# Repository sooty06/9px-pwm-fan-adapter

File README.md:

# 9px-pwm-fan-adapter
PWM fan adapter for replacing the stock fans in an Eaton 9PX series UPS.

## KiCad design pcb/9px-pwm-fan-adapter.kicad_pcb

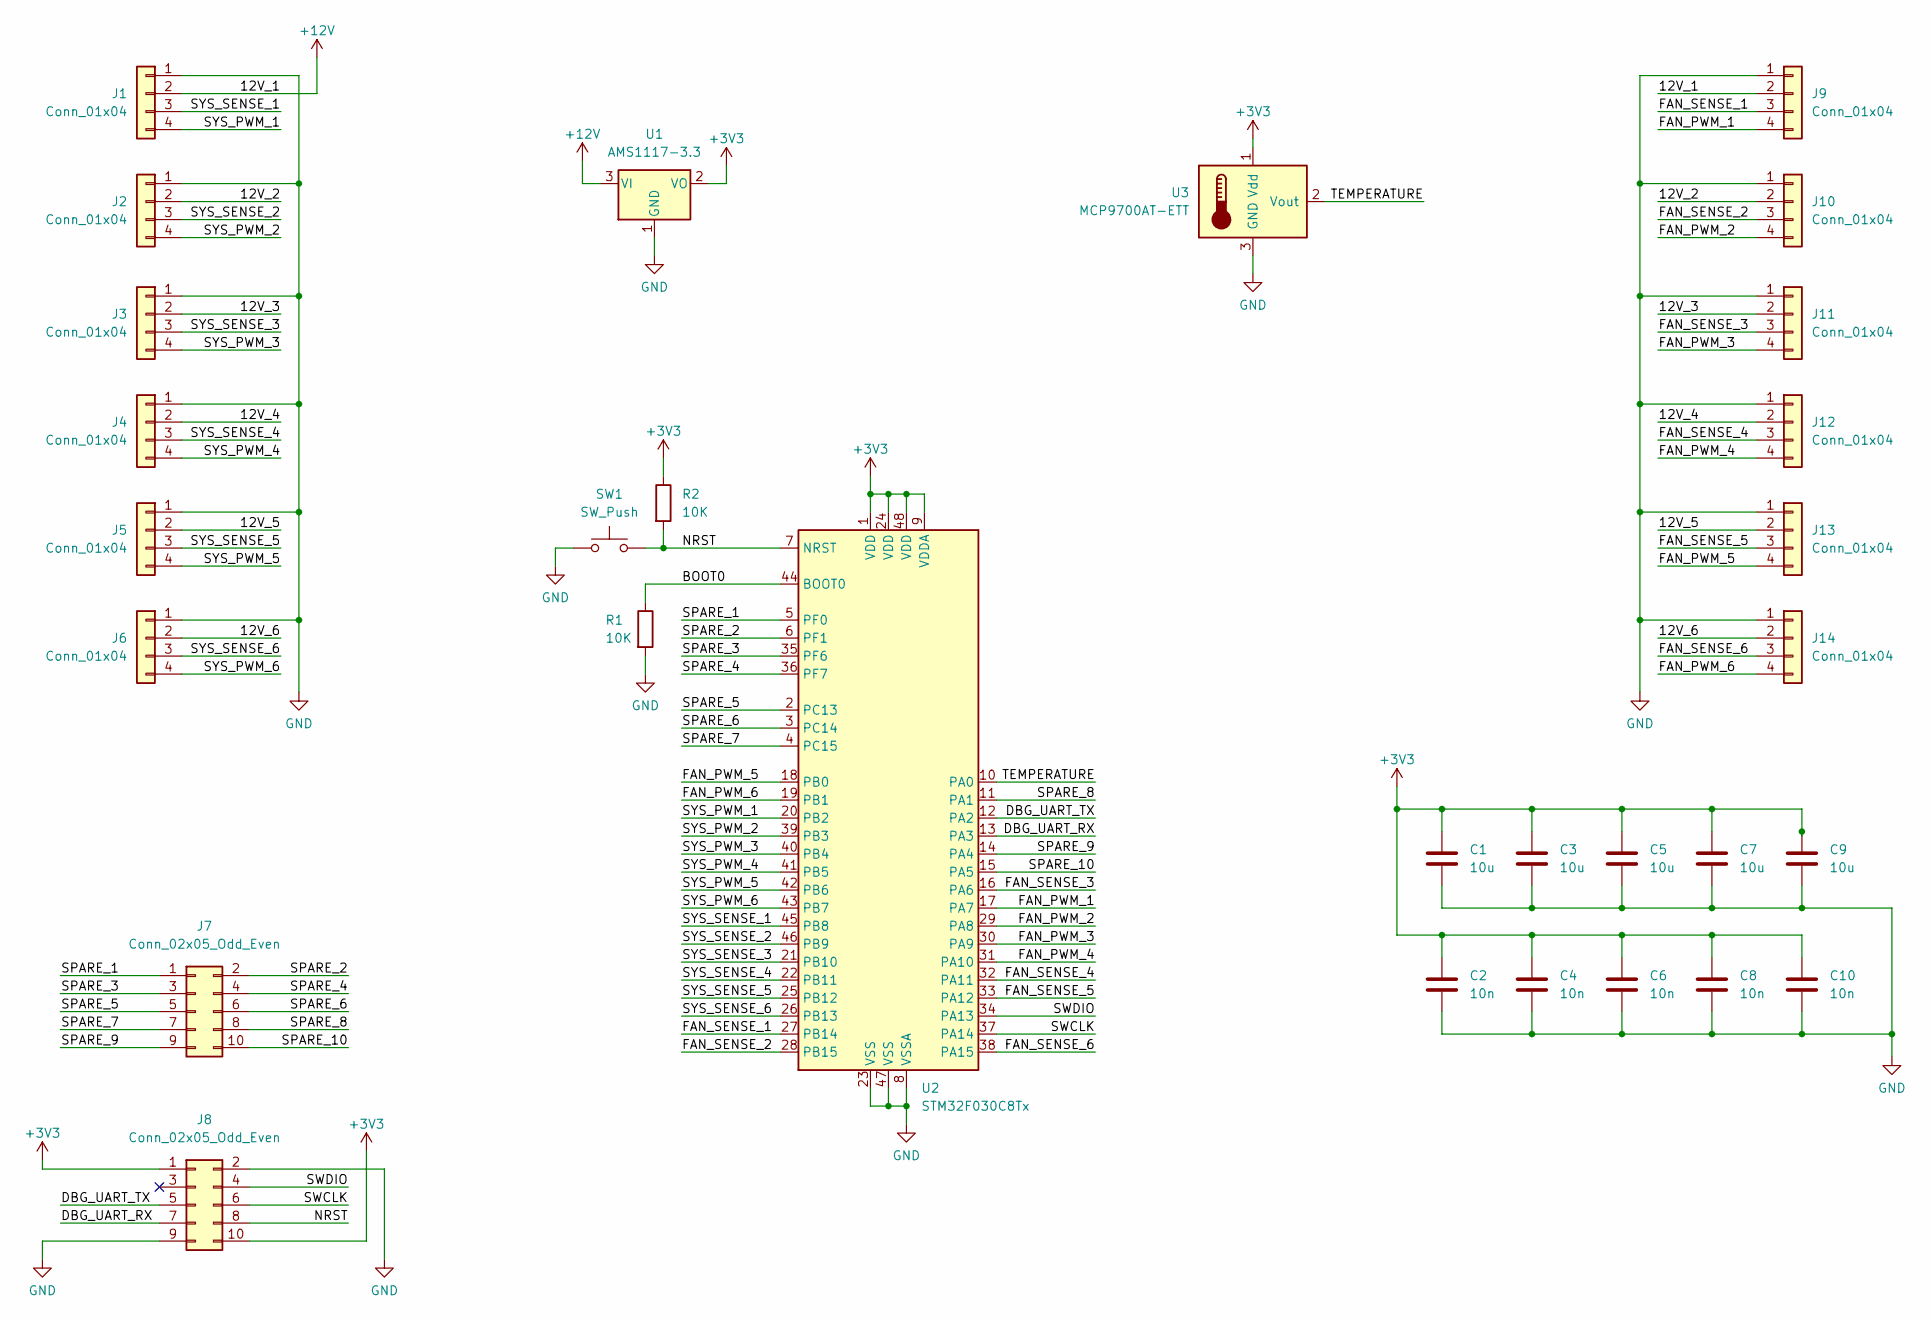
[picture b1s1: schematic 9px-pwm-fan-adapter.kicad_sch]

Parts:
C1, C3, C5, C7, C9: 10u; C_0603_1608Metric
C2, C4, C6, C8, C10: 10n; C_0603_1608Metric
J1, J2, J3, J4, J5, J6, J9, J10, J11, J12, J13, J14: Conn_01x04; Molex_KK-254_AE-6410-04A_1x04_P2.54mm_Vertical
J7, J8: Conn_02x05_Odd_Even; PinHeader_2x05_P2.54mm_Vertical
R1, R2: 10K; R_0603_1608Metric
SW1: SW_Push; SW-SMD_4P-L5.1-W5.1-P3.70-LS6.5-TL-2
U1: AMS1117-3.3; SOT-223-3_TabPin2
U2: STM32F030C8Tx; LQFP-48_7x7mm_P0.5mm
U3: MCP9700AT-ETT; SOT-23

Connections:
+3V3: C1.1, C2.1, C3.1, C4.1, C5.1, C6.1, C7.1, C8.1, C9.1, C10.1, J8.1, J8.10, R2.1, U1.2 (VO), U2.1 (VDD), U2.9 (VDDA), U2.24 (VDD), U2.48 (VDD), U3.1 (Vdd)
+12V: J1.2, J9.2, U1.3 (VI)
/12V_2: J2.2, J10.2
/12V_3: J3.2, J11.2
/12V_4: J4.2, J12.2
/12V_5: J5.2, J13.2
/12V_6: J6.2, J14.2
/BOOT0: R1.1, U2.44 (BOOT0)
/DBG_UART_RX: J8.7, U2.13 (PA3)
/DBG_UART_TX: J8.5, U2.12 (PA2)
/FAN_PWM_1: J9.4, U2.17 (PA7)
/FAN_PWM_2: J10.4, U2.29 (PA8)
/FAN_PWM_3: J11.4, U2.30 (PA9)
/FAN_PWM_4: J12.4, U2.31 (PA10)
/FAN_PWM_5: J13.4, U2.18 (PB0)
/FAN_PWM_6: J14.4, U2.19 (PB1)
/FAN_SENSE_1: J9.3, U2.27 (PB14)
/FAN_SENSE_2: J10.3, U2.28 (PB15)
/FAN_SENSE_3: J11.3, U2.16 (PA6)
/FAN_SENSE_4: J12.3, U2.32 (PA11)
/FAN_SENSE_5: J13.3, U2.33 (PA12)
/FAN_SENSE_6: J14.3, U2.38 (PA15)
/NRST: J8.8, R2.2, SW1.2, U2.7 (NRST)
/SPARE_1: J7.1, U2.5 (PF0)
/SPARE_2: J7.2, U2.6 (PF1)
/SPARE_3: J7.3, U2.35 (PF6)
/SPARE_4: J7.4, U2.36 (PF7)
/SPARE_5: J7.5, U2.2 (PC13)
/SPARE_6: J7.6, U2.3 (PC14)
/SPARE_7: J7.7, U2.4 (PC15)
/SPARE_8: J7.8, U2.11 (PA1)
/SPARE_9: J7.9, U2.14 (PA4)
/SPARE_10: J7.10, U2.15 (PA5)
/SWCLK: J8.6, U2.37 (PA14)
/SWDIO: J8.4, U2.34 (PA13)
/SYS_PWM_1: J1.4, U2.20 (PB2)
/SYS_PWM_2: J2.4, U2.39 (PB3)
/SYS_PWM_3: J3.4, U2.40 (PB4)
/SYS_PWM_4: J4.4, U2.41 (PB5)
/SYS_PWM_5: J5.4, U2.42 (PB6)
/SYS_PWM_6: J6.4, U2.43 (PB7)
/SYS_SENSE_1: J1.3, U2.45 (PB8)
/SYS_SENSE_2: J2.3, U2.46 (PB9)
/SYS_SENSE_3: J3.3, U2.21 (PB10)
/SYS_SENSE_4: J4.3, U2.22 (PB11)
/SYS_SENSE_5: J5.3, U2.25 (PB12)
/SYS_SENSE_6: J6.3, U2.26 (PB13)
/TEMPERATURE: U2.10 (PA0), U3.2 (Vout)
GND: C1.2, C2.2, C3.2, C4.2, C5.2, C6.2, C7.2, C8.2, C9.2, C10.2, J1.1, J2.1, J3.1, J4.1, J5.1, J6.1, J8.2, J8.9, J9.1, J10.1, J11.1, J12.1, J13.1, J14.1, R1.2, SW1.1, U1.1 (GND), U2.8 (VSSA), U2.23 (VSS), U2.47 (VSS), U3.3 (GND)

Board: 2 copper layers, 30 parts (0 on the bottom side), 49 nets, no tracks yet.

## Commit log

2022-06-01 Modification to limit KiCAD gitignore comment to PCB folder.
2022-06-01 Initial start to electronic design. Project created and components chosen.
2022-06-03 Remove unnecessary folder.
2022-06-03 New auto generated file...
2022-06-03 Add custom library for JLCPCB pushbutton.
2022-06-03 Schematic finished and moved to PCB design.
